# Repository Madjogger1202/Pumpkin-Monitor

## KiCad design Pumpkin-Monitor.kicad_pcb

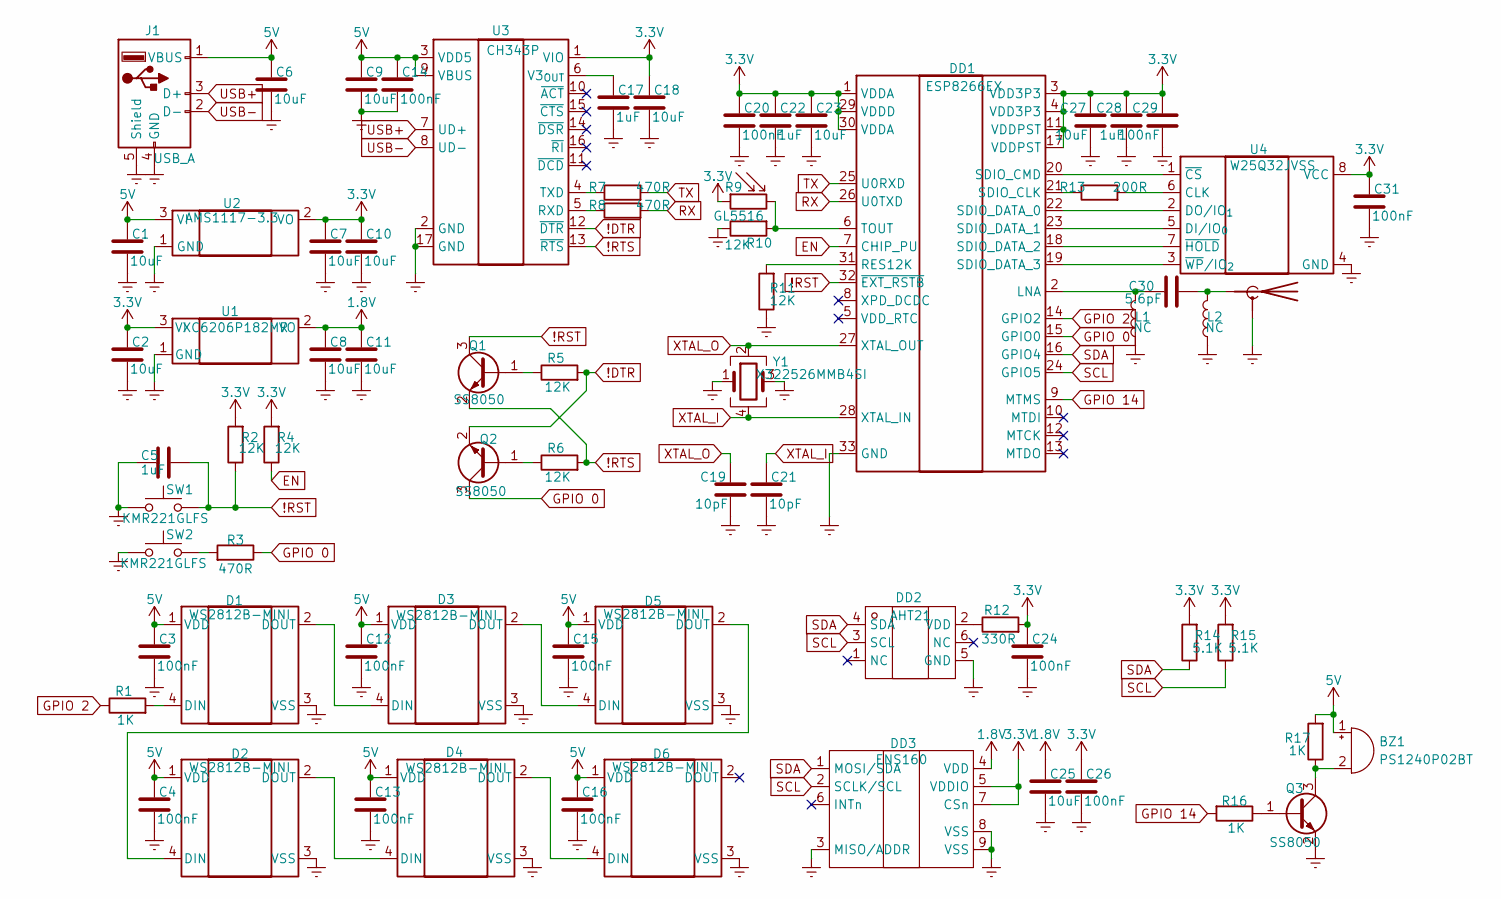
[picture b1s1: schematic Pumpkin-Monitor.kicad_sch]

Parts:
AE1: Antenna_Shield; Texas_SWRA117D_2.4GHz_Left
BZ1: PS1240P02BT; Buzzer_TDK_PS1240P02BT_D12.2mm_H6.5mm
C1, C2, C6, C7, C8, C9, C10, C11, C18, C23, C25, C27: 10uF; C_0402_1005Metric
C3, C4, C12, C13, C14, C15, C16, C20, C24, C26, C29, C31: 100nF; C_0402_1005Metric
C5, C17, C22, C28: 1uF; C_0402_1005Metric
C19, C21: 10pF; C_0402_1005Metric
C30: 5.6pF; C_0201_0603Metric
D1, D2, D3, D4, D5, D6: WS2812B-MINI; LED_WS2812B-Mini_PLCC4_3.5x3.5mm
DD1: ESP8266EX; QFN-32-1EP_5x5mm_P0.5mm_EP3.45x3.45mm
DD2: AHT21; Manufacturer Part AHT21; LCSC Part Name AHT21
DD3: ENS160; Manufacturer Part ENS160-BGLT; LCSC Part Name ENS160-BGLT
J1: USB_A; USB_A_CNCTech_1001-011-01101_Horizontal
L1, L2: NC; L_0201_0603Metric
Q1, Q2, Q3: SS8050; SOT-23
R1, R16, R17: 1K; R_0402_1005Metric
R2, R4, R5, R6, R10, R11: 12K; R_0402_1005Metric
R3, R7, R8: 470R; R_0402_1005Metric
R9: GL5516; R_LDR_5.1x4.3mm_P3.4mm_Vertical
R12: 330R; R_0402_1005Metric
R13: 200R; R_0402_1005Metric
R14, R15: 5.1K; R_0402_1005Metric
SW1, SW2: KMR221GLFS; SW_SPST_PTS810
U1: XC6206P182MR; SOT-23-3
U2: AMS1117-3.3; SOT-89-3
U3: CH343P; WCH_QFN-16-1EP_3x3mm_P0.5mm_EP1.8x1.8mm
U4: W25Q32JVSS; SOIC-8_5.3x5.3mm_P1.27mm
Y1: X322526MMB4SI; Crystal_SMD_3225-4Pin_3.2x2.5mm

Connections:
1.8V: C8.1, C11.1, C25.1, DD3.4 (VDD), U1.2 (VO)
3.3V: C2.1, C7.1, C10.1, C18.1, C20.1, C22.1, C23.1, C24.1, C26.1, C27.1, C28.1, C29.1, C31.1, DD1.1 (VDDA), DD1.3 (VDD3P3), DD1.4 (VDD3P3), DD1.11 (VDDPST), DD1.17 (VDDPST), DD1.29 (VDDD), DD1.30 (VDDA), DD3.5 (VDDIO), DD3.7 (CSn), R2.2, R4.2, R9.1, R12.2, R14.2, R15.2, U1.3 (VI), U2.2 (VO), U3.1 (VIO), U4.8 (VCC)
5V: BZ1.1 (+), C1.1, C3.1, C4.1, C6.1, C9.1, C12.1, C13.1, C14.1, C15.1, C16.1, D1.1 (VDD), D2.1 (VDD), D3.1 (VDD), D4.1 (VDD), D5.1 (VDD), D6.1 (VDD), J1.1 (VBUS), R17.2, U2.3 (VI), U3.3 (VDD5), U3.9 (VBUS)
!DTR: Q2.2 (E), R5.2, U3.12 (~DTR)
!RST: C5.1, DD1.32 (~EXT_RSTB), Q1.3 (C), R2.1, SW1.2
!RTS: Q1.2 (E), R6.2, U3.13 (~RTS)
EN: DD1.7 (CHIP_PU), R4.1
Earth: AE1.2 (Shield), C1.2, C2.2, C3.2, C4.2, C5.2, C6.2, C7.2, C8.2, C9.2, C10.2, C11.2, C12.2, C13.2, C14.2, C15.2, C16.2, C17.2, C18.2, C19.2, C20.2, C21.2, C22.2, C23.2, C24.2, C25.2, C26.2, C27.2, C28.2, C29.2, C31.2, D1.3 (VSS), D2.3 (VSS), D3.3 (VSS), D4.3 (VSS), D5.3 (VSS), D6.3 (VSS), DD1.33 (GND), DD2.5 (GND), DD3.3 (MISO/ADDR), DD3.8 (VSS), DD3.9 (VSS), J1.4 (GND), J1.5 (Shield), L1.1, L2.1, Q3.2 (E), R10.1, R11.1, SW1.1, SW2.1, U1.1 (GND), U2.1 (GND), U3.2 (GND), U3.17 (GND), U4.4 (GND), Y1.1, Y1.3
GPIO 0: DD1.15 (GPIO0), Q2.3 (C), R3.1
GPIO 2: DD1.14 (GPIO2), R1.1
GPIO 14: DD1.9 (MTMS), R16.2
unnamed: AE1.1 (A), C30.2, L2.2
unnamed: BZ1.2 (-), Q3.3 (C), R17.1
unnamed: D1.4 (DIN), R1.2
unnamed: D1.2 (DOUT), D3.4 (DIN)
unnamed: D2.4 (DIN), D5.2 (DOUT)
unnamed: D2.2 (DOUT), D4.4 (DIN)
unnamed: D3.2 (DOUT), D5.4 (DIN)
unnamed: D4.2 (DOUT), D6.4 (DIN)
unnamed: C30.1, DD1.2 (LNA), L1.2
unnamed: DD1.31 (RES12K), R11.2
unnamed: DD1.21 (SDIO_CLK), R13.1
unnamed: DD1.20 (SDIO_CMD), U4.1 (~CS)
unnamed: DD1.22 (SDIO_DATA_0), U4.2 (DO/IO_{1})
unnamed: DD1.23 (SDIO_DATA_1), U4.5 (DI/IO_{0})
unnamed: DD1.18 (SDIO_DATA_2), U4.7 (~HOLD)
unnamed: DD1.19 (SDIO_DATA_3), U4.3 (~WP/IO_{2})
unnamed: DD1.6 (TOUT), R9.2, R10.2
unnamed: DD2.2 (VDD), R12.1
unnamed: Q1.1 (B), R5.1
unnamed: Q2.1 (B), R6.1
unnamed: Q3.1 (B), R16.1
unnamed: R3.2, SW2.2
unnamed: R8.1, U3.5 (RXD)
unnamed: R7.1, U3.4 (TXD)
unnamed: C17.1, U3.6 (V3_{OUT})
unnamed: R13.2, U4.6 (CLK)
RX: DD1.26 (U0TXD), R8.2
SCL: DD1.24 (GPIO5), DD2.3 (SCL), DD3.2 (SCLK/SCL), R15.1
SDA: DD1.16 (GPIO4), DD2.4 (SDA), DD3.1 (MOSI/SDA), R14.1
TX: DD1.25 (U0RXD), R7.2
USB+: J1.3 (D+), U3.7 (UD+)
USB-: J1.2 (D-), U3.8 (UD-)
XTAL_I: C21.1, DD1.28 (XTAL_IN), Y1.4
XTAL_O: C19.1, DD1.27 (XTAL_OUT), Y1.2

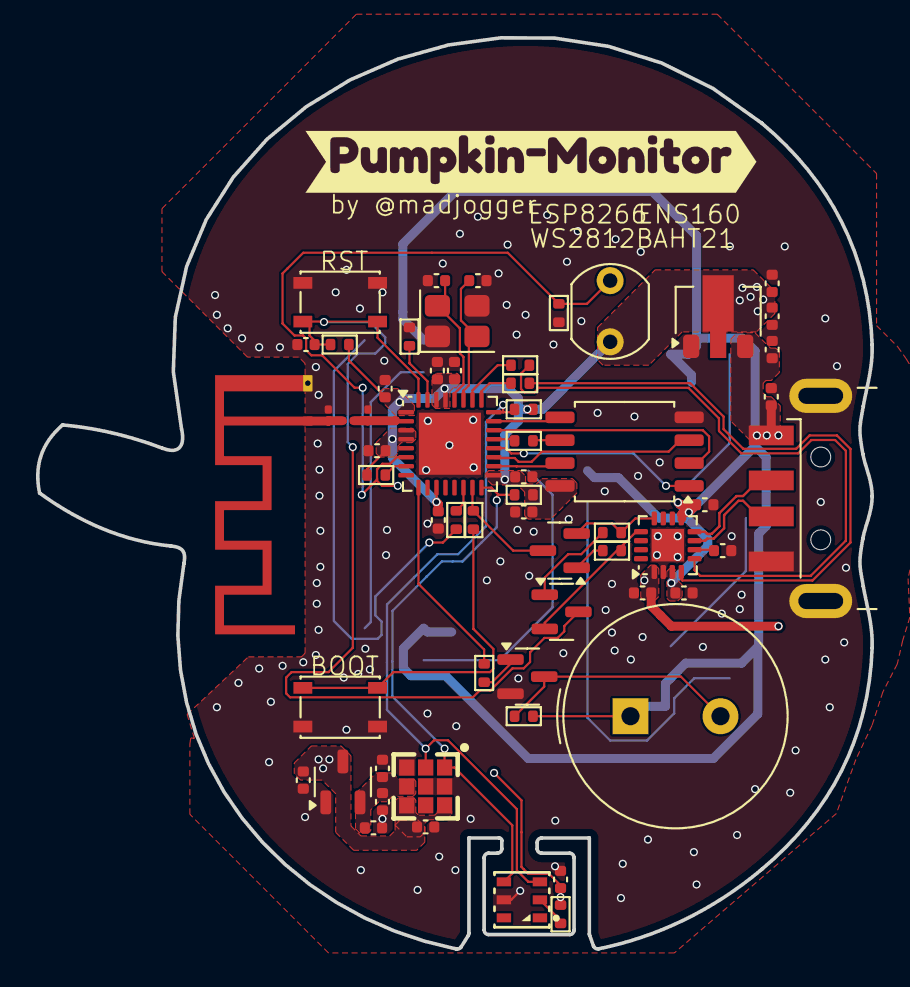
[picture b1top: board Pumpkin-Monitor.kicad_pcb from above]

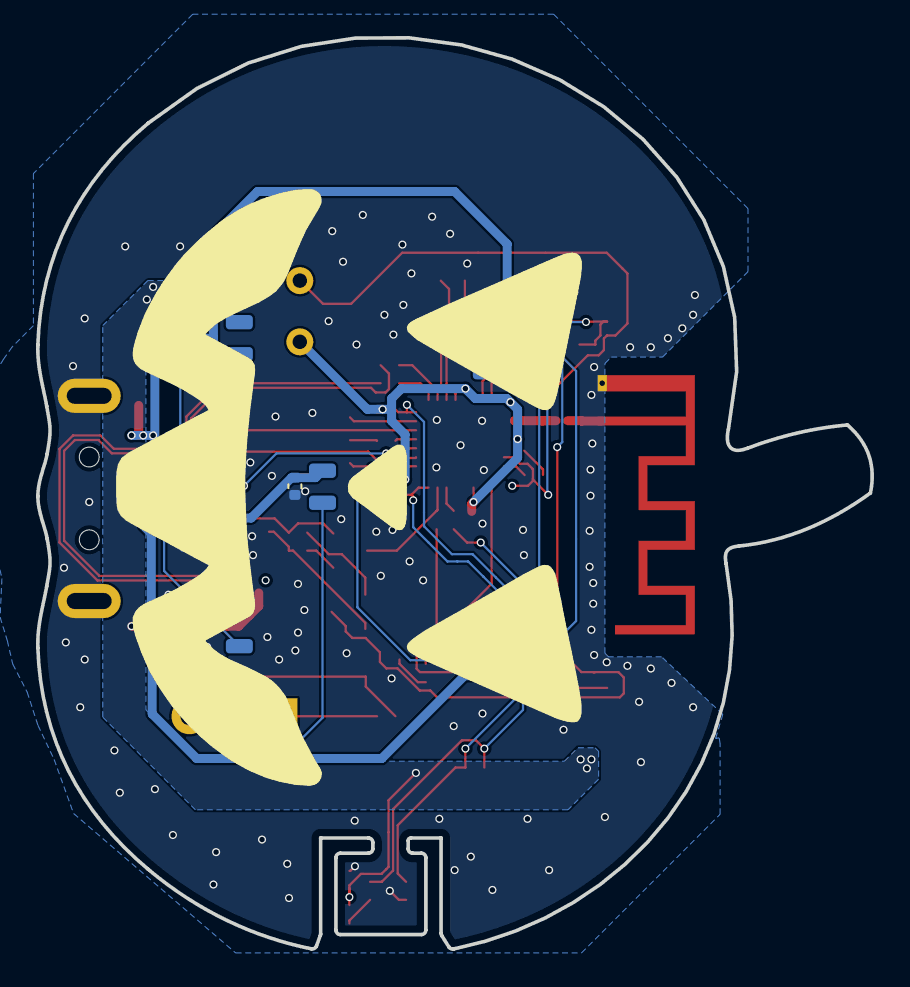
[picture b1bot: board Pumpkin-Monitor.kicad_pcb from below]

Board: 2 copper layers, 46.4 x 50.6 mm, 73 parts (12 on the bottom side), 45 nets.

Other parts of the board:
kibuzzard-690A31FE: G***; kibuzzard-690A31FE

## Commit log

2025-11-04 rev0 ready
2025-11-04 corrected GND connection of ESP8266 ( added vias to bulky polygons )
